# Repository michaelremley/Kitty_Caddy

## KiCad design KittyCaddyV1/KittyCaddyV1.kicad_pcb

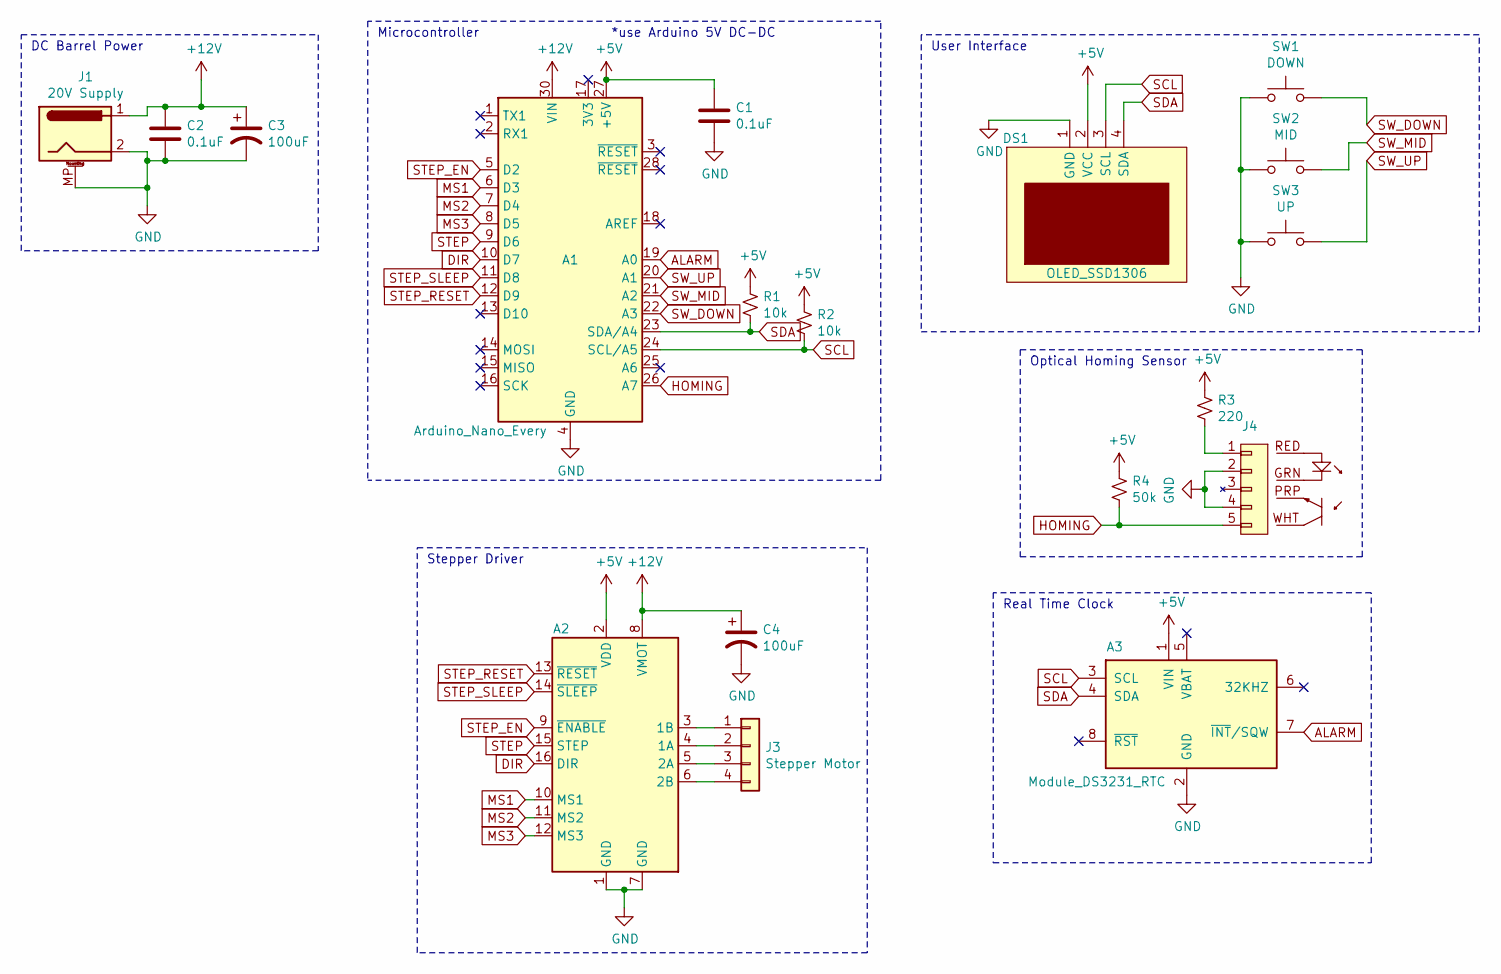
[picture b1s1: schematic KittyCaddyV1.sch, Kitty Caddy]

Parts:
A1: Arduino_Nano_Every; Arduino_Nano
A2: Pololu_Breakout_A4988; Pololu_Breakout-16_15.2x20.3mm
A3: Module_DS3231_RTC; PinSocket_1x08_P2.54mm_Vertical
C1, C2: 0.1uF; C_Rect_L4.6mm_W2.0mm_P2.50mm_MKS02_FKP02
C3, C4: 100uF; CP_Radial_D6.3mm_P2.50mm
DS1: OLED_SSD1306; SSD1306
J1: 20V Supply; BarrelJack_CUI_PJ-102AH_Horizontal
J3: Stepper Motor; Molex_KK-254_AE-6410-04A_1x04_P2.54mm_Vertical
J4: OPB740_Reflective_Object_Sensor; Molex_KK-254_AE-6410-05A_1x05_P2.54mm_Vertical
R1, R2: 10k; R_Axial_DIN0204_L3.6mm_D1.6mm_P7.62mm_Horizontal
R3: 220; R_Axial_DIN0204_L3.6mm_D1.6mm_P7.62mm_Horizontal
R4: 50k; R_Axial_DIN0204_L3.6mm_D1.6mm_P7.62mm_Horizontal
SW1: DOWN; SW_PUSH_6mm_H9.5mm
SW2: MID; SW_PUSH_6mm_H9.5mm
SW3: UP; SW_PUSH_6mm_H9.5mm

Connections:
+5V: A1.27 (+5V), A2.2 (VDD), A3.1 (VIN), C1.1, DS1.2 (VCC), R1.2, R2.2, R3.2, R4.2
+12V: A1.30 (VIN), A2.8 (VMOT), C2.1, C3.1, C4.1, J1.1
ALARM: A1.19 (A0), A3.7 (~INT~/SQW)
DIR: A1.10 (D7), A2.16 (DIR)
GND: A1.4 (GND), A1.29 (GND), A2.1 (GND), A2.7 (GND), A3.2 (GND), C1.2, C2.2, C3.2, C4.2, DS1.1 (GND), J1.2, J1.MP (MountPin), J4.2, J4.4, SW1.1, SW2.1, SW3.1
HOMING: A1.26 (A7), J4.5, R4.1
MS1: A1.6 (D3), A2.10 (MS1)
MS2: A1.7 (D4), A2.11 (MS2)
MS3: A1.8 (D5), A2.12 (MS3)
unnamed: A2.3 (1B), J3.1
unnamed: A2.4 (1A), J3.2
unnamed: A2.5 (2A), J3.3
unnamed: A2.6 (2B), J3.4
unnamed: J4.1, R3.1
SCL: A1.24 (SCL/A5), A3.3 (SCL), DS1.3 (SCL), R2.1
SDA: A1.23 (SDA/A4), A3.4 (SDA), DS1.4 (SDA), R1.1
STEP: A1.9 (D6), A2.15 (STEP)
STEP_EN: A1.5 (D2), A2.9 (~ENABLE)
STEP_RESET: A1.12 (D9), A2.13 (~RESET)
STEP_SLEEP: A1.11 (D8), A2.14 (~SLEEP)
SW_DOWN: A1.22 (A3), SW1.2
SW_MID: A1.21 (A2), SW2.2
SW_UP: A1.20 (A1), SW3.2

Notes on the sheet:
User Interface
Real Time Clock
Optical Homing Sensor
Stepper Driver
DC Barrel Power
*use Arduino 5V DC-DC
Microcontroller

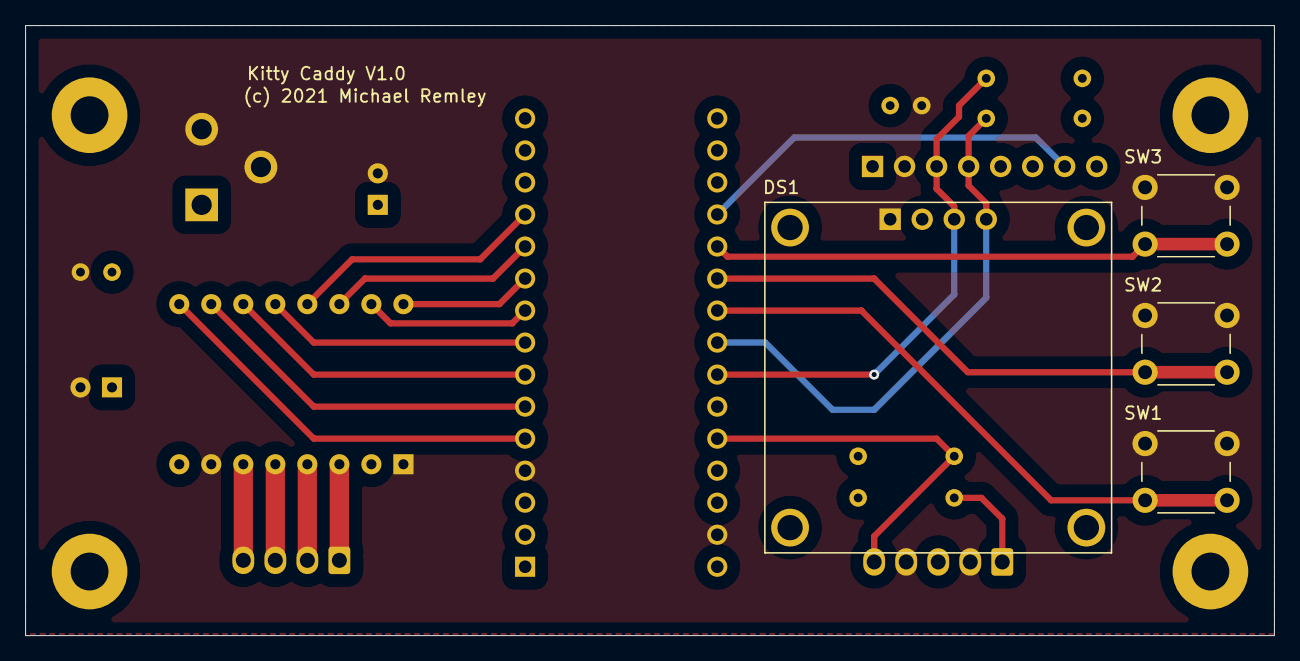
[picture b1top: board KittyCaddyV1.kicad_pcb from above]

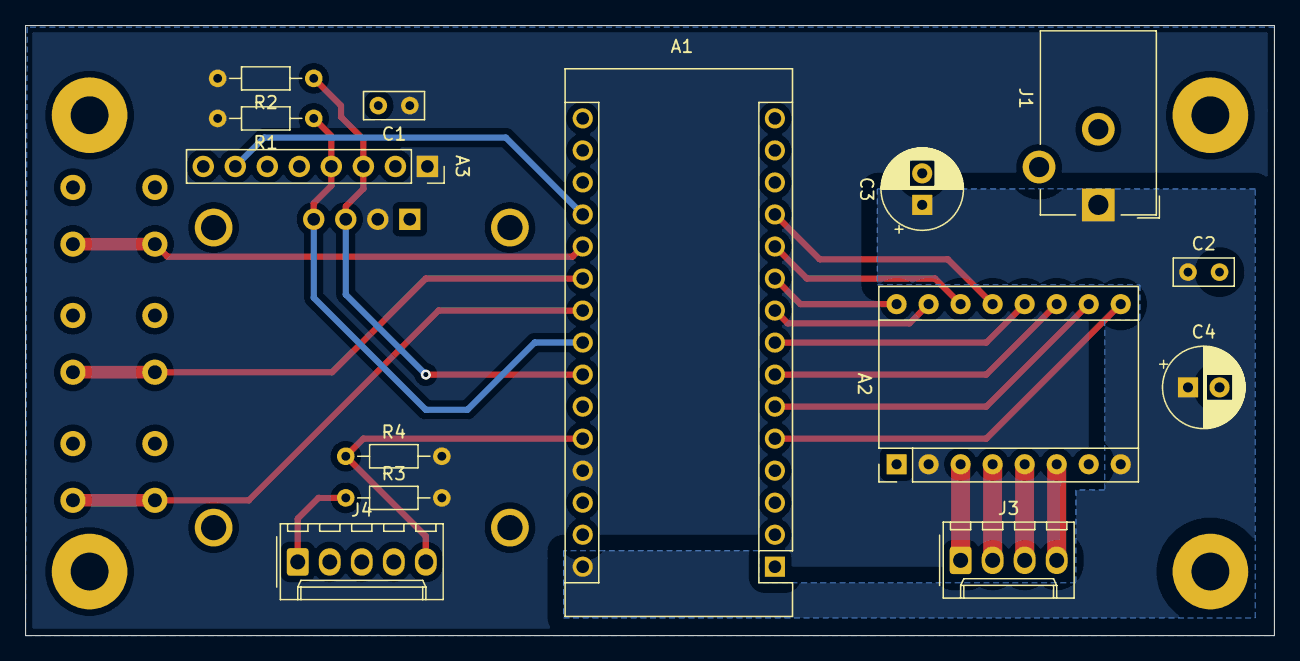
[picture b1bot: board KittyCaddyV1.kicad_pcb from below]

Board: 2 copper layers, 99.1 x 48.4 mm, 18 parts (14 on the bottom side), 23 nets.

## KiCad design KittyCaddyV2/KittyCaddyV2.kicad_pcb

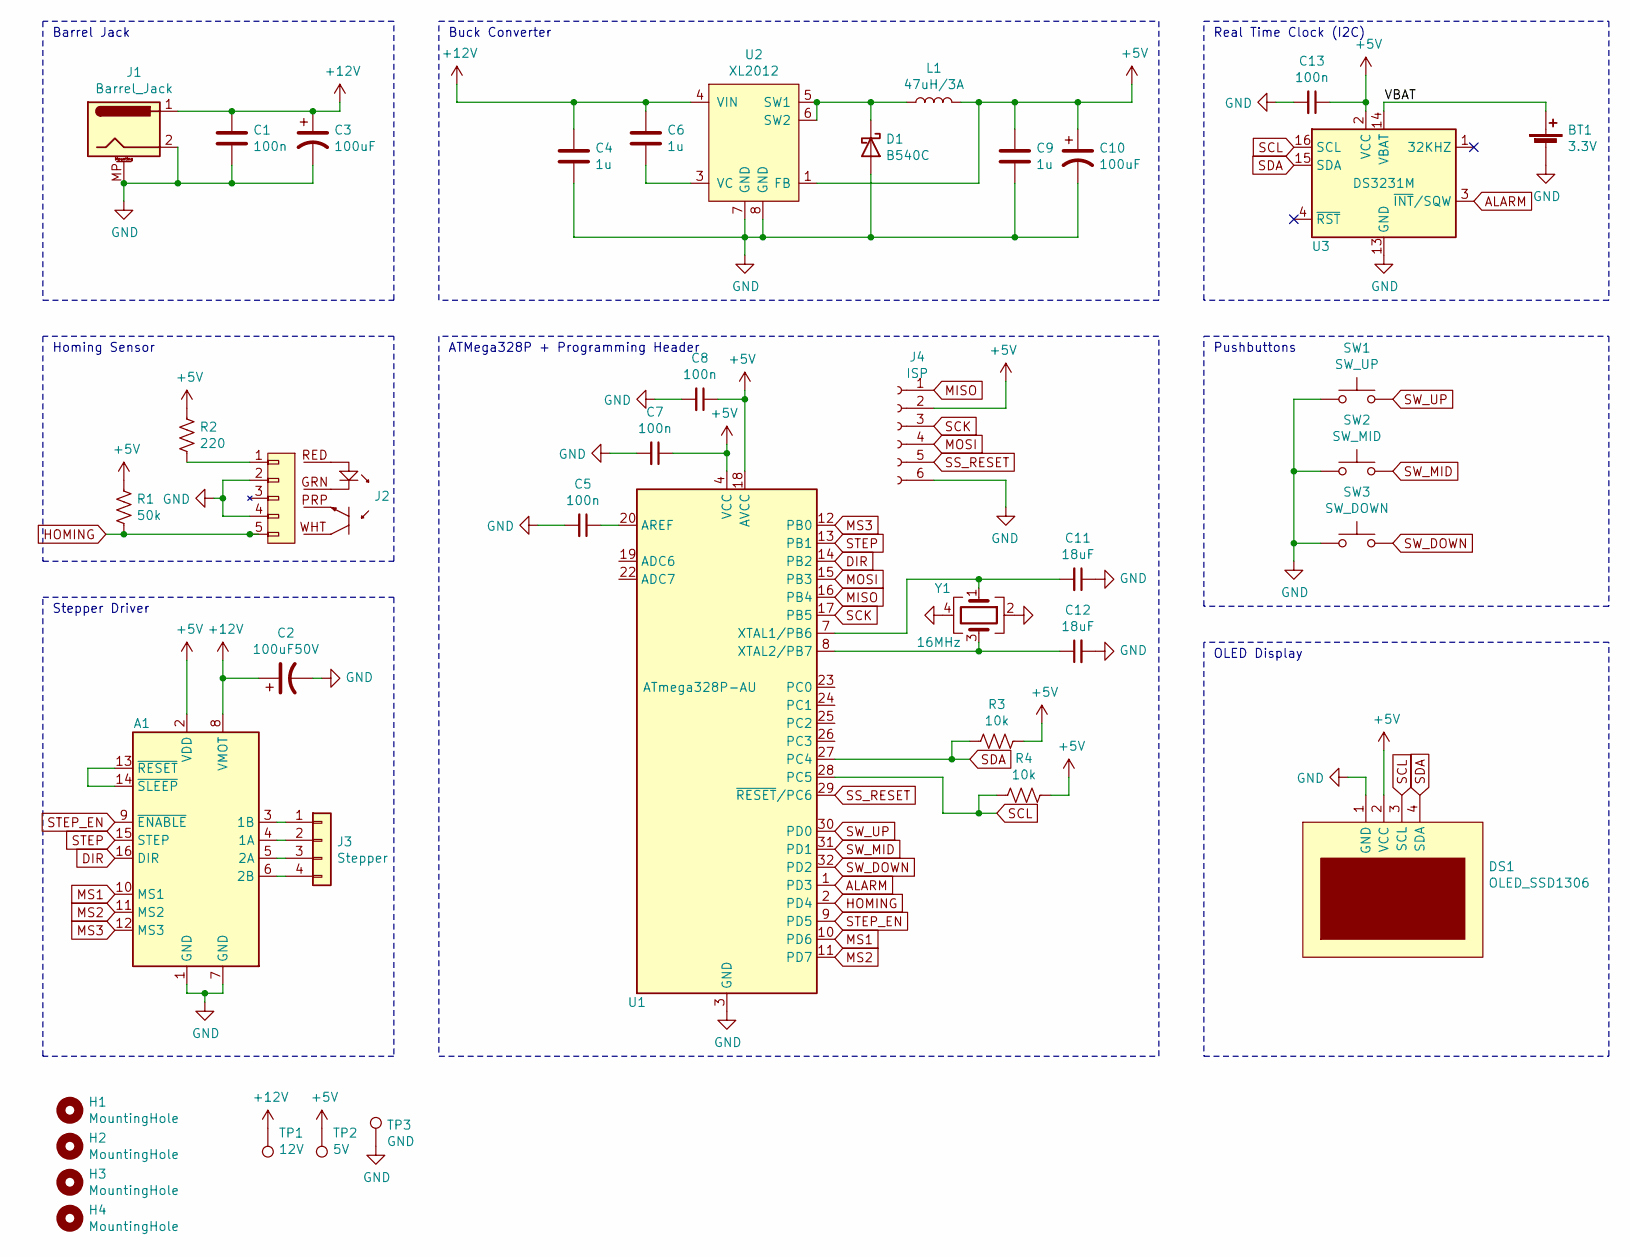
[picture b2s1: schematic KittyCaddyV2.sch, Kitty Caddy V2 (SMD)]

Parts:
A1: Pololu_Breakout-16_15.2x20.3mm
BT1: 3.3V; Keystone_2997_LR44_Holder_THT
C1, C5, C7, C8, C13: 100n; C_0805_2012Metric
C2: 100uF50V; CP_Radial_D8.0mm_P3.50mm
C3, C10: 100uF; CP_Radial_D8.0mm_P3.50mm
C4, C6, C9: 1u; C_0805_2012Metric
C11, C12: 18uF; C_0805_2012Metric
D1: B540C; D_2010_5025Metric_Castellated
DS1: OLED_SSD1306; SSD1306
H1, H2, H3, H4: MountingHole; MountingHole_3mm_Pad
J1: Barrel_Jack; BarrelJack_CUI_PJ-102AH_Horizontal
J2: OPB740_Reflective_Object_Sensor; Molex_KK-254_AE-6410-05A_1x05_P2.54mm_Vertical
J3: Stepper; Molex_KK-254_AE-6410-04A_1x04_P2.54mm_Vertical
J4: ISP; PinHeader_2x03_P2.54mm_Vertical
L1: 47uH/3A; Inductor_Panasonic_12mm_x_11mm
R1: 50k; R_0805_2012Metric
R2: 220; R_0805_2012Metric
R3, R4: 10k; R_0805_2012Metric
SW1: SW_UP; SW_PUSH_6mm_H9.5mm
SW2: SW_MID; SW_PUSH_6mm_H9.5mm
SW3: SW_DOWN; SW_PUSH_6mm_H9.5mm
TP1: 12V; TestPoint_Plated_Hole_D2.0mm
TP2: 5V; TestPoint_Plated_Hole_D2.0mm
TP3: GND; TestPoint_Plated_Hole_D2.0mm
U1: ATmega328P-AU; TQFP-32_7x7mm_P0.8mm
U2: XL2012; SOIC-8_3.9x4.9mm_P1.27mm
U3: DS3231M; SOIC-16W_7.5x10.3mm_P1.27mm
Y1: 16MHz; Crystal_SMD_3225-4Pin_3.2x2.5mm

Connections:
+5V: A1.2 (VDD), C7.1, C8.1, C9.1, C10.1, C13.1, DS1.2 (VCC), J4.2, L1.2, R1.1, R2.1, R3.1, R4.1, TP2.1, U1.4 (VCC), U1.6 (VCC), U1.18 (AVCC), U2.1 (FB), U3.2 (VCC)
+12V: A1.8 (VMOT), C1.1, C2.1, C3.1, C4.1, C6.1, J1.1, TP1.1, U2.4 (VIN)
/VBAT: BT1.1 (+), U3.14 (VBAT)
ALARM: U1.1 (PD3), U3.3 (~INT~/SQW)
DIR: A1.16 (DIR), U1.14 (PB2)
GND: A1.1 (GND), A1.7 (GND), BT1.2 (-), C1.2, C2.2, C3.2, C4.2, C5.2, C7.2, C8.2, C9.2, C10.2, C11.1, C12.2, C13.2, D1.2 (A), DS1.1 (GND), J1.2, J1.MP (MountPin), J2.2, J2.4, J4.6, SW1.1, SW2.1, SW3.1, TP3.1, U1.3 (GND), U1.5 (GND), U1.21 (GND), U2.7 (GND), U2.8 (GND), U3.5 (GND), U3.6 (GND), U3.7 (GND), U3.8 (GND), U3.9 (GND), U3.10 (GND), U3.11 (GND), U3.12 (GND), U3.13 (GND), Y1.2, Y1.4
HOMING: J2.5, R1.2, U1.2 (PD4)
MISO: J4.1, U1.16 (PB4)
MOSI: J4.4, U1.15 (PB3)
MS1: A1.10 (MS1), U1.10 (PD6)
MS2: A1.11 (MS2), U1.11 (PD7)
MS3: A1.12 (MS3), U1.12 (PB0)
unnamed: A1.3 (1B), J3.1
unnamed: A1.4 (1A), J3.2
unnamed: A1.5 (2A), J3.3
unnamed: A1.6 (2B), J3.4
unnamed: A1.13 (~RESET), A1.14 (~SLEEP)
unnamed: C5.1, U1.20 (AREF)
unnamed: C6.2, U2.3 (VC)
unnamed: C11.2, U1.7 (XTAL1/PB6), Y1.1
unnamed: C12.1, U1.8 (XTAL2/PB7), Y1.3
unnamed: D1.1 (K), L1.1, U2.5 (SW1), U2.6 (SW2)
unnamed: J2.1, R2.2
SCK: J4.3, U1.17 (PB5)
SCL: DS1.3 (SCL), R4.2, U1.28 (PC5), U3.16 (SCL)
SDA: DS1.4 (SDA), R3.2, U1.27 (PC4), U3.15 (SDA)
SS_RESET: J4.5, U1.29 (~RESET~/PC6)
STEP: A1.15 (STEP), U1.13 (PB1)
STEP_EN: A1.9 (~ENABLE), U1.9 (PD5)
SW_DOWN: SW3.2, U1.32 (PD2)
SW_MID: SW2.2, U1.31 (PD1)
SW_UP: SW1.2, U1.30 (PD0)

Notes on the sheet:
OLED Display
Pushbuttons
Real Time Clock (I2C)
ATMega328P + Programming Header
Buck Converter
Barrel Jack
Homing Sensor
Stepper Driver

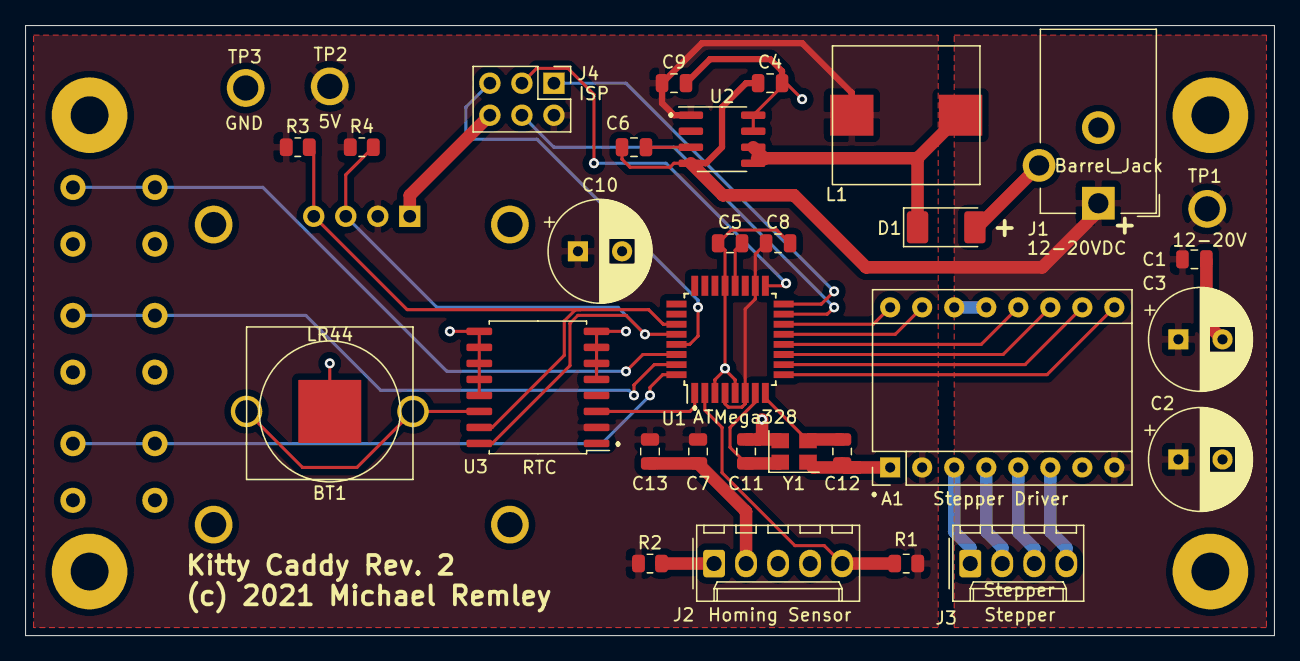
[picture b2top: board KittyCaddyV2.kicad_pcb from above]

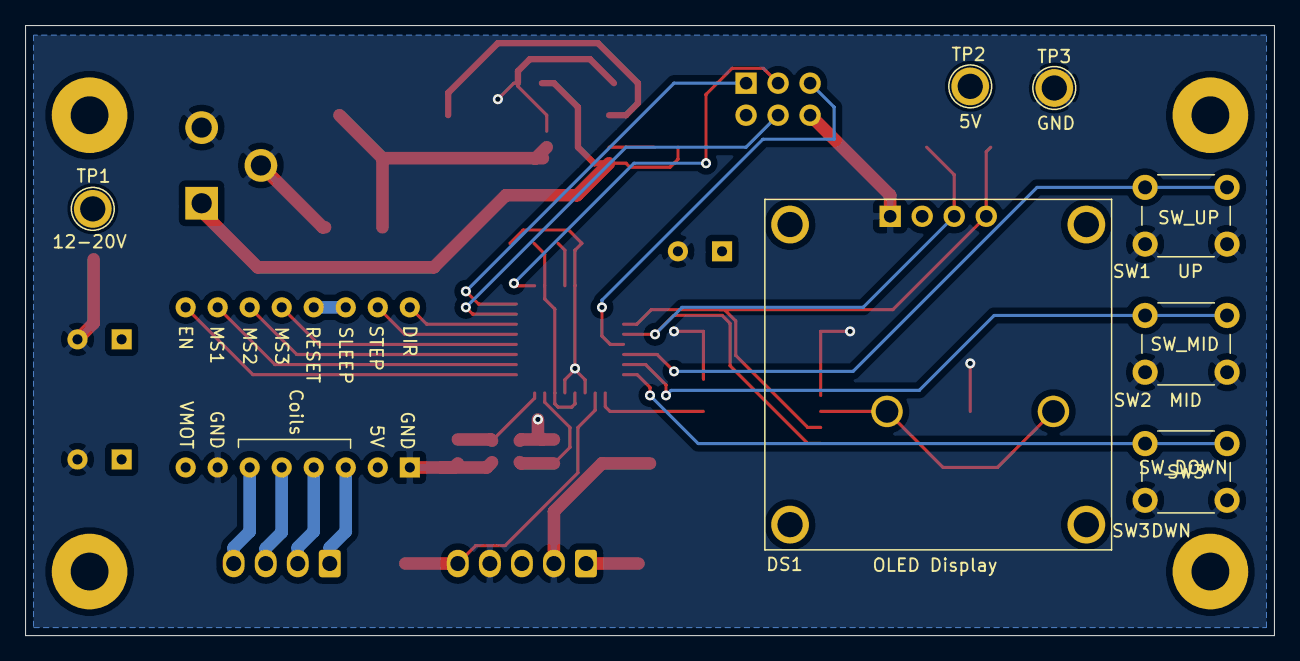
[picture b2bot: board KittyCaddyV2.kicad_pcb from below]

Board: 2 copper layers, 99.1 x 48.4 mm, 40 parts (7 on the bottom side), 32 nets.

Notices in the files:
KittyCaddyV1/KittyCaddyV1.kicad_pcb:
(c) 2021 Michael Remley
